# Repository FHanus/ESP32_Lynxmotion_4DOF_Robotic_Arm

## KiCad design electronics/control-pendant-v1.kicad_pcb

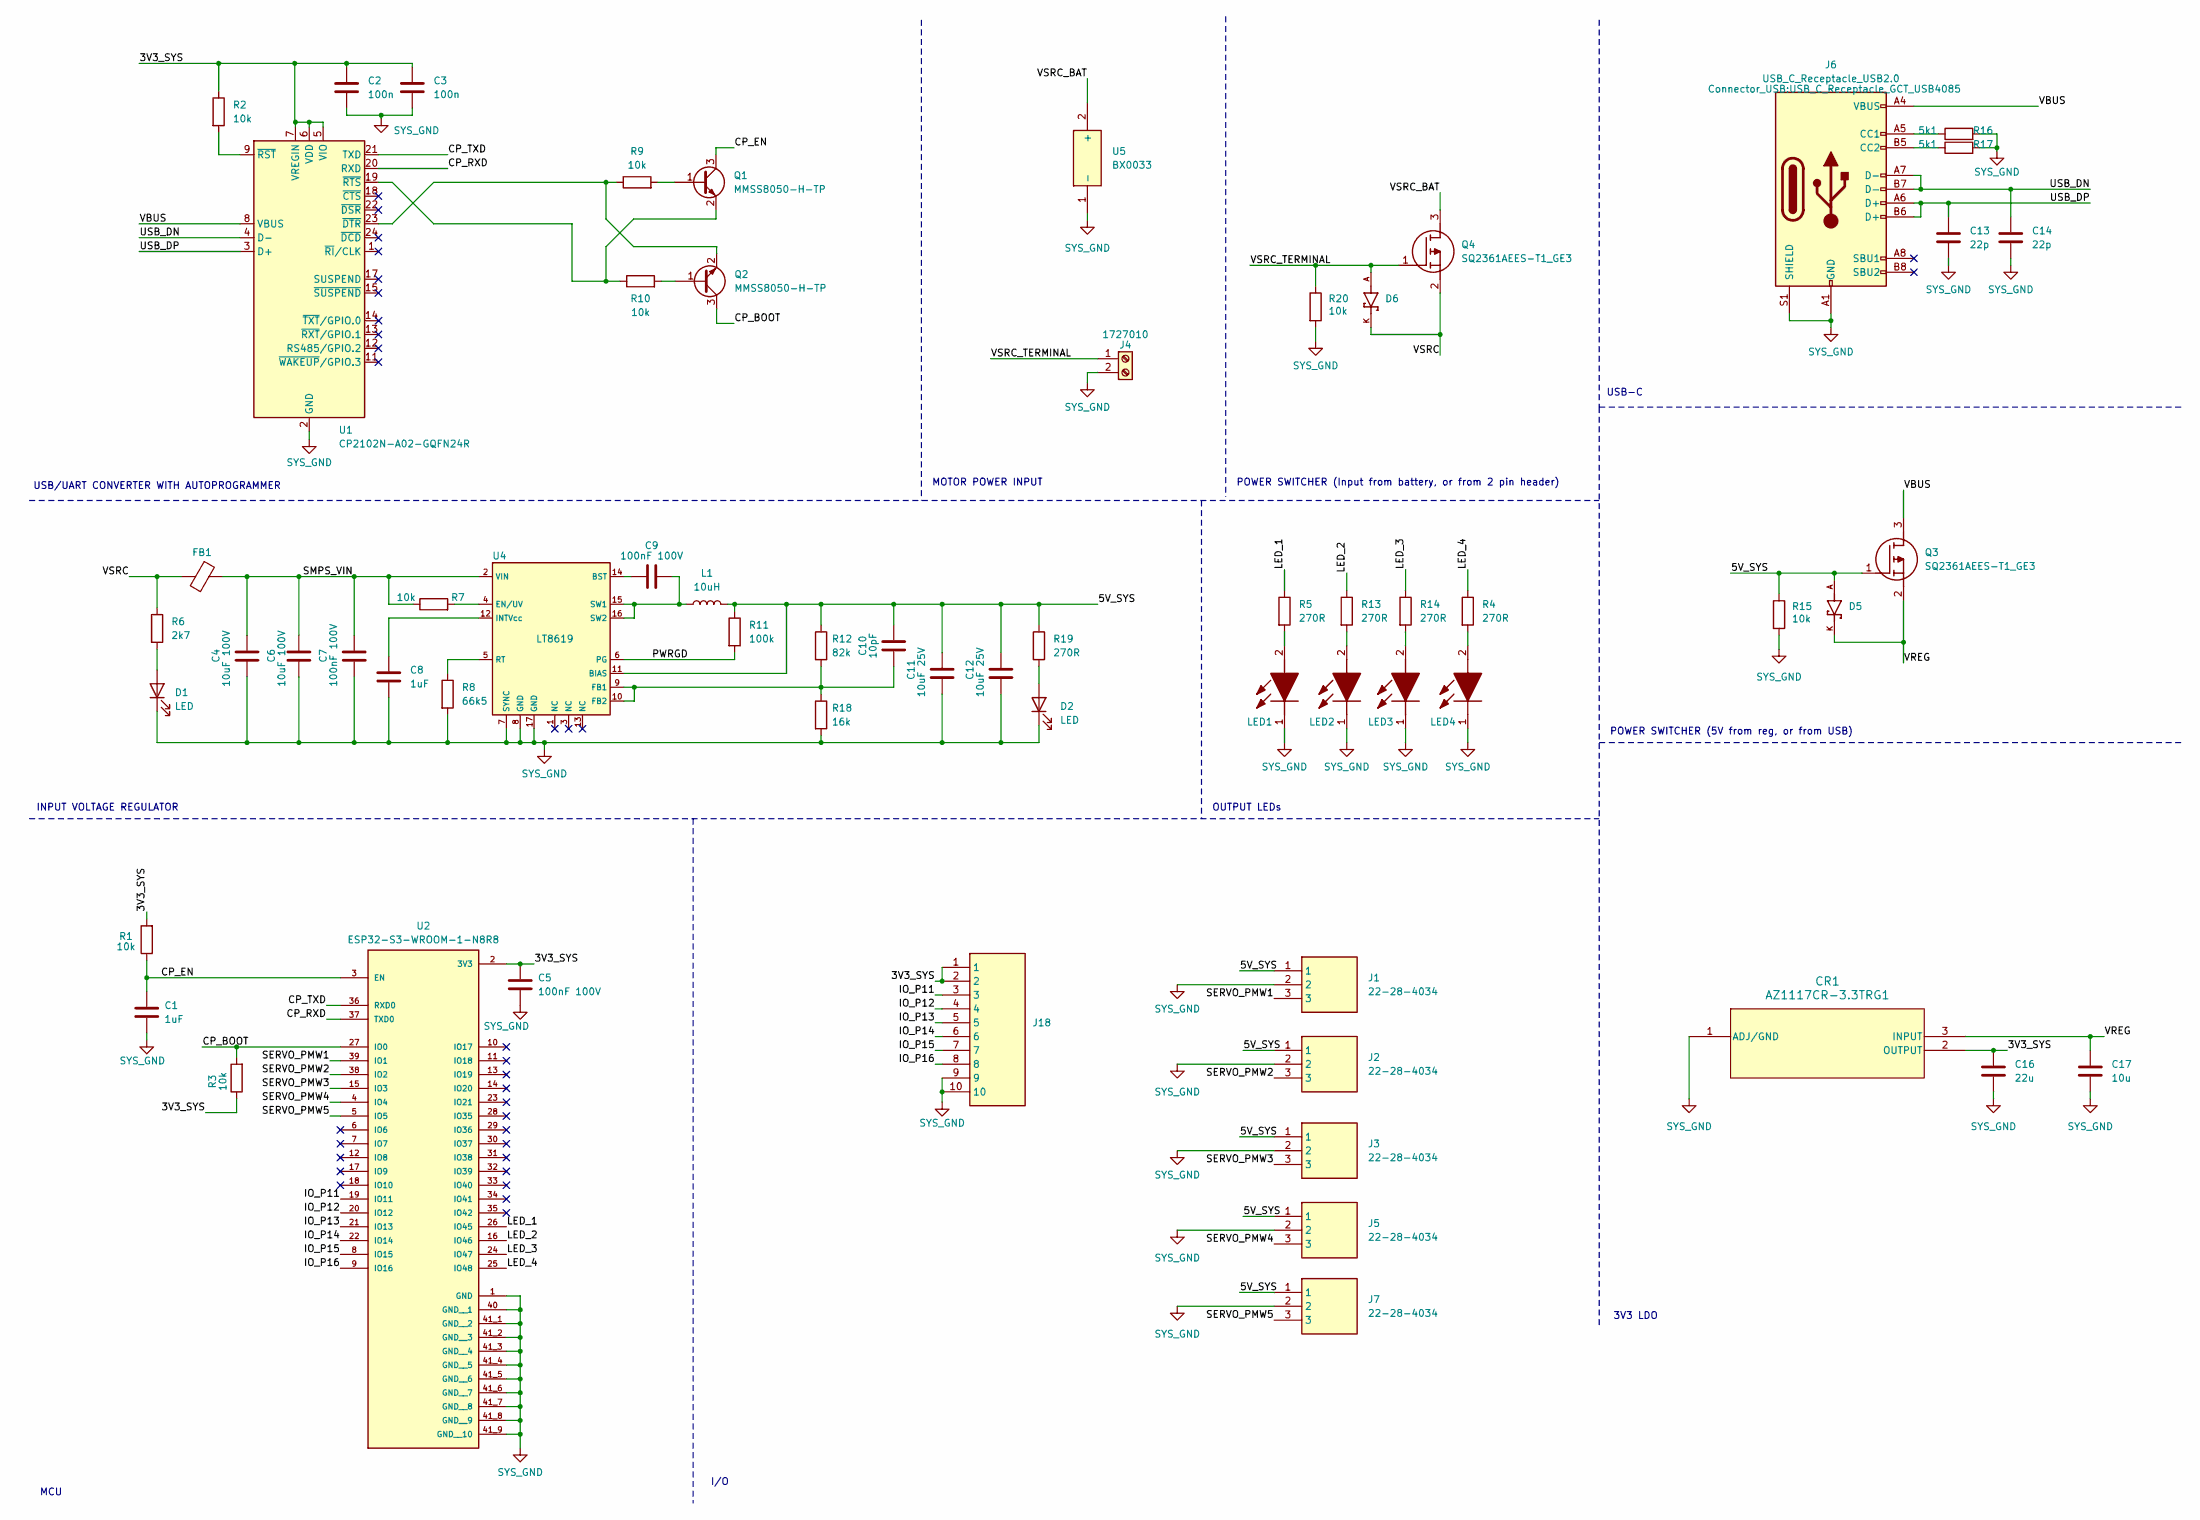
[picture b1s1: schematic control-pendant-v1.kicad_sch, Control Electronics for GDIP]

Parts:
C1, C8: 1uF; C_0603_1608Metric
C2, C3: 100n; C_0402_1005Metric
C4, C6: 10uF 100V; C_1210_3225Metric
C5, C7, C9: 100nF 100V; C_0603_1608Metric
C10: 10pF; C_0603_1608Metric
C11, C12: 10uF 25V; C_0603_1608Metric
C13, C14: 22p; C_0402_1005Metric
C16: 22u; C_0402_1005Metric
C17: 10u; C_0402_1005Metric
CR1: AZ1117CR-3.3TRG1; SOT89_AZ1117_DIO
D1, D2: LED; LED_0603_1608Metric
D5, D6: PMEG3020EH_115; PMEG3020EH_115_DIO_PMEG3020EH_115
FB1: MAF1608GAD121LTAH0; L_0603_1608Metric
J1, J2, J3, J5, J7: 22-28-4034; HDRV3W66P0X254_1X3_762X249X1042P; Mouser Part Number 538-22-28-4034
J4: 1727010
J6: USB_C_Receptacle_USB2.0; USB_C_Receptacle_GCT_USB4085
J18: M20-7821042; SHDR10W70P0X254_1X10_2580X250X865P; Mouser Part Number 855-M20-7821042
L1: 10uH; NRS4018T100MDGJ
LED1, LED2, LED3, LED4: TLHG5420-ASZ; TLHG5420ASZ; Mouser Part Number 78-TLHG5420-ASZ
Q1, Q2: MMSS8050-H-TP; TNPN_SOT-23_MCC
Q3, Q4: SQ2361AEES-T1_GE3; SOT95P237X112-3N; Mouser Part Number 78-SQ2361AEES-T1_GE3
R1, R3, R7: 10k; R_0603_1608Metric
R2, R9, R10, R15, R20: 10k; R_0402_1005Metric
R4, R5, R13, R14: 270R; R_0402_1005Metric
R6: 2k7; R_1206_3216Metric
R8: 66k5; R_0603_1608Metric
R11: 100k; R_0603_1608Metric
R12: 82k; R_0603_1608Metric
R16, R17: 5k1; R_0402_1005Metric
R18: 16k; R_0603_1608Metric
R19: 270R; R_0603_1608Metric
U1: CP2102N-A02-GQFN24R; QFN-24-1EP_4x4mm_P0.5mm_EP2.6x2.6mm
U2: ESP32-S3-WROOM-1-N8R8; ESP32-S3-WROOM-1-N8R8_XCVR_ESP32S3WROOM1N8R8
U4: LT8619; SOP50P490X110-17N
U5: BX0033; Mouser Part Number 122-BX0033

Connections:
/3V3_SYS: C2.1, C3.1, C5.1, C16.1, CR1.2 (OUTPUT), J18.1, J18.2, R1.2, R2.1, R3.1, U1.5 (VIO), U1.6 (VDD), U1.7 (VREGIN), U2.2 (3V3)
/5V_SYS: C10.2, C11.1, C12.1, D5.A, J1.1, J2.1, J3.1, J5.1, J7.1, L1.2, Q3.1 (G), R11.1, R12.1, R15.1, R19.1, U4.11 (BIAS)
/CP_BOOT: Q2.3 (C), R3.2, U2.27 (IO0)
/CP_EN: C1.1, Q1.3 (C), R1.1, U2.3 (EN)
/CP_RXD: U1.20 (RXD), U2.37 (TXD0)
/CP_TXD: U1.21 (TXD), U2.36 (RXD0)
/IO_P11: J18.3, U2.19 (IO11)
/IO_P12: J18.4, U2.20 (IO12)
/IO_P13: J18.5, U2.21 (IO13)
/IO_P14: J18.6, U2.22 (IO14)
/IO_P15: J18.7, U2.8 (IO15)
/IO_P16: J18.8, U2.9 (IO16)
/LED_1: R5.1, U2.26 (IO45)
/LED_2: R13.1, U2.16 (IO46)
/LED_3: R14.1, U2.24 (IO47)
/LED_4: R4.1, U2.25 (IO48)
/PWRGD: R11.2, U4.6 (PG)
/SERVO_PMW1: J1.3, U2.39 (IO1)
/SERVO_PMW2: J2.3, U2.38 (IO2)
/SERVO_PMW3: J3.3, U2.15 (IO3)
/SERVO_PMW4: J5.3, U2.4 (IO4)
/SERVO_PMW5: J7.3, U2.5 (IO5)
/SMPS_VIN: C4.1, C6.1, C7.1, FB1.1, R7.1, U4.2 (VIN)
/USB_DN: C14.1, J6.A7 (D-), J6.B7 (D-), U1.4 (D-)
/USB_DP: C13.1, J6.A6 (D+), J6.B6 (D+), U1.3 (D+)
/VBUS: J6.A4 (VBUS), J6.A9 (VBUS), J6.B4 (VBUS), J6.B9 (VBUS), Q3.3 (D), U1.8 (VBUS)
/VREG: C17.1, CR1.3 (INPUT), D5.K, Q3.2 (S)
/VSRC: D6.K, FB1.2, Q4.2 (S), R6.1
/VSRC_BAT: Q4.3 (D), U5.2 (+)
/VSRC_TERMINAL: D6.A, J4.1, Q4.1 (G), R20.1
unnamed: D1.2 (A), R6.2
unnamed: D2.2 (A), R19.2
unnamed: J6.A5 (CC1), R16.1
unnamed: J6.B5 (CC2), R17.1
unnamed: LED1.2 (A), R5.2
unnamed: LED2.2 (A), R13.2
unnamed: LED3.2 (A), R14.2
unnamed: LED4.2 (A), R4.2
unnamed: Q1.1 (B), R9.2
unnamed: Q1.2 (E), R10.1, U1.19 (~RTS)
unnamed: Q2.1 (B), R10.2
unnamed: Q2.2 (E), R9.1, U1.23 (~DTR)
unnamed: R2.2, U1.9 (~RST)
unnamed: C9.1, U4.14 (BST)
unnamed: R7.2, U4.4 (EN/UV)
unnamed: C10.1, R12.2, R18.1, U4.9 (FB1), U4.10 (FB2)
unnamed: C8.1, U4.12 (INTVcc)
unnamed: R8.1, U4.5 (RT)
unnamed: C9.2, L1.1, U4.15 (SW1), U4.16 (SW2)
SYS_GND: C1.2, C2.2, C3.2, C4.2, C5.2, C6.2, C7.2, C8.2, C11.2, C12.2, C13.2, C14.2, C16.2, C17.2, CR1.1 (ADJ/GND), D1.1 (K), D2.1 (K), J1.2, J2.2, J3.2, J4.2, J5.2, J6.A1 (GND), J6.A12 (GND), J6.B1 (GND), J6.B12 (GND), J6.S1 (SHIELD), J7.2, J18.9, J18.10, LED1.1 (K), LED2.1 (K), LED3.1 (K), LED4.1 (K), R8.2, R15.2, R16.2, R17.2, R18.2, R20.2, U1.2 (GND), U1.25 (GND), U2.1 (GND), U2.40 (GND__1), U2.41_1 (GND__2), U2.41_2 (GND__3), U2.41_3 (GND__4), U2.41_4 (GND__5), U2.41_5 (GND__6), U2.41_6 (GND__7), U2.41_7 (GND__8), U2.41_8 (GND__9), U2.41_9 (GND__10), U2.41_10, U2.41_11, U2.41_12, U2.41_13, U2.41_14, U2.41_15, U2.41_16, U2.41_17, U2.41_18, U2.41_19, U2.41_20, U2.41_21, U4.7 (SYNC), U4.8 (GND), U4.17 (GND), U5.1 (-)

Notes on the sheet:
OUTPUT LEDs
I/O
3V3 LDO
USB/UART CONVERTER WITH AUTOPROGRAMMER
USB-C
POWER SWITCHER (5V from reg, or from USB)
MOTOR POWER INPUT
INPUT VOLTAGE REGULATOR
MCU
POWER SWITCHER (Input from battery, or from 2 pin header)

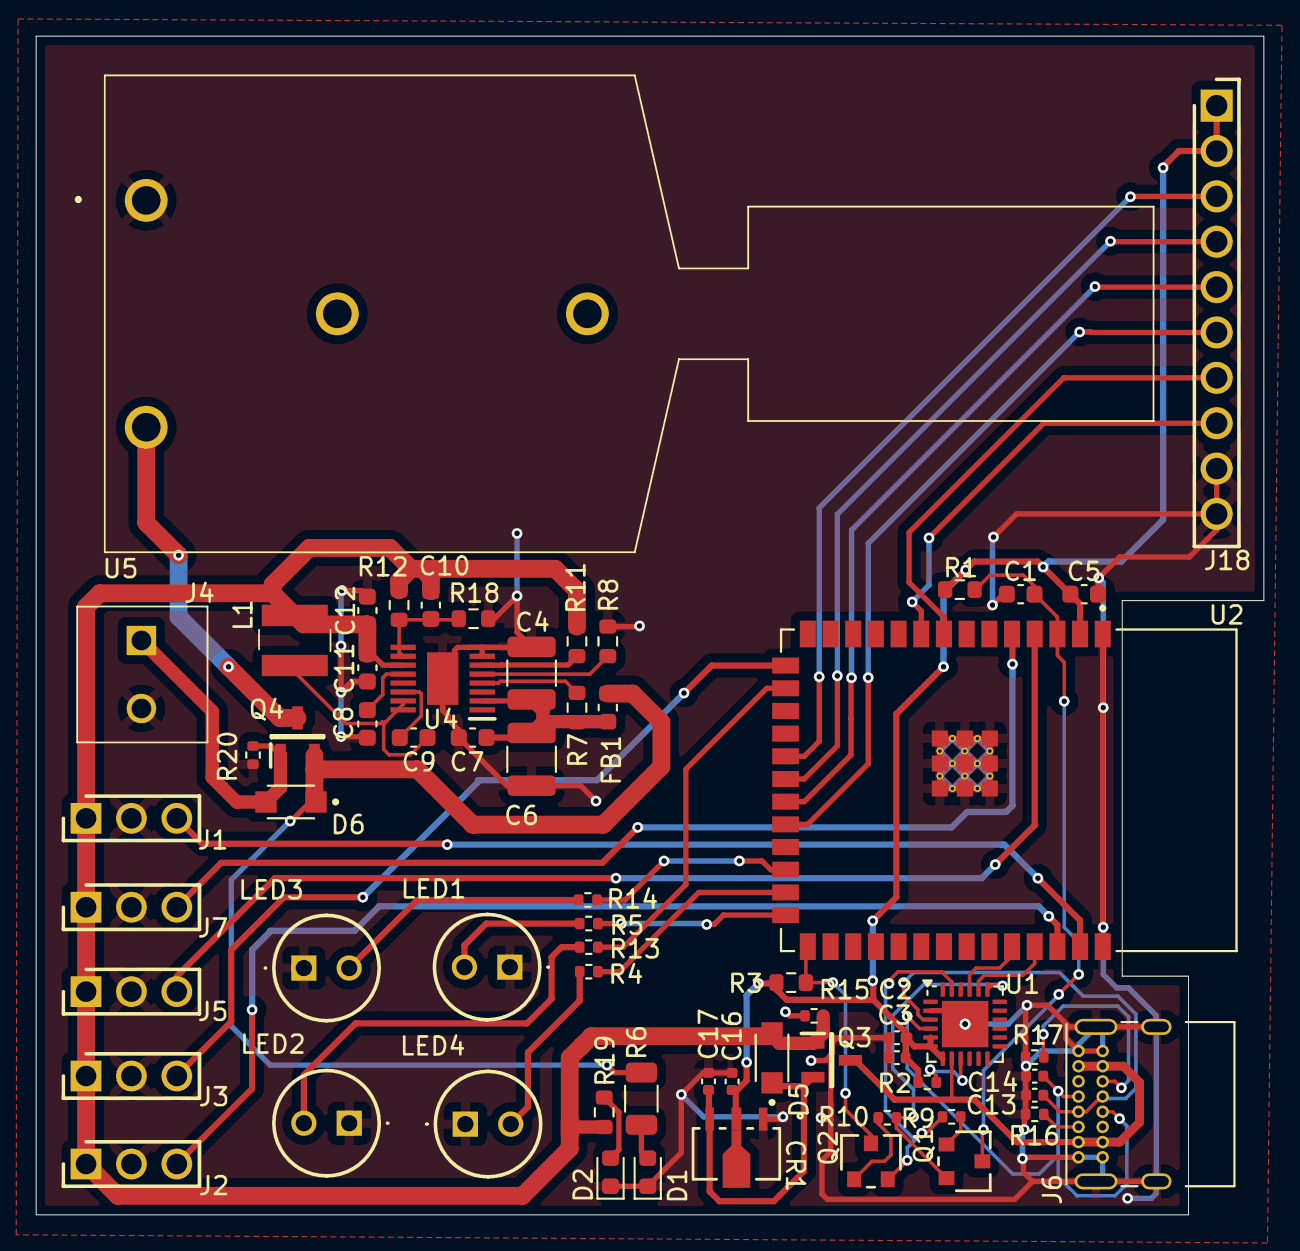
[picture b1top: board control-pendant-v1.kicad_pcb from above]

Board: 2 copper layers, 68.7 x 66.0 mm, 63 parts (0 on the bottom side), 50 nets.

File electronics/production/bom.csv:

Designator,Footprint,Value,Quantity,Link
"C1, C8",603,1uF,2,https://www.mouser.co.uk/ProductDetail/KYOCERA-AVX/06036C105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
C10,603,10pF,1,https://www.mouser.co.uk/ProductDetail/KYOCERA-AVX/0603YA100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
"C11, C12",603,10uF 25V,2,https://www.mouser.co.uk/ProductDetail/Murata-Electronics/GR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
"C13, C14",402,22p,2,https://www.mouser.co.uk/ProductDetail/KYOCERA-AVX/04025A220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
C16,402,22u,1,https://www.mouser.co.uk/ProductDetail/TAIYO-YUDEN/MEASP105C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
C17,402,10u,1,https://www.mouser.co.uk/ProductDetail/Murata-Electronics/GR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
"C2, C3",402,100n,2,https://www.mouser.co.uk/ProductDetail/KYOCERA-AVX/04025C104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
"C4, C6",1210,10uF 100V,2,https://www.mouser.co.uk/ProductDetail/Walsin/1210B106K160CT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
"C5, C7, C9",603,100nF 100V,3,https://www.mouser.co.uk/ProductDetail/TAIYO-YUDEN/MAJCH168B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
CR1,SOT89_AZ1117_DIO,AZ1117CR-3.3TRG1,1,https://www.mouser.co.uk/ProductDetail/Diodes-Incorporated/A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
"D1, D2",603,LED,2,https://www.mouser.co.uk/ProductDetail/VCC/LSM0603412V?qs=%2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
"D5, D6",PMEG3020EH_115_DIO_PMEG3020EH_115,PMEG3020EH_115,2,https://www.mouser.co.uk/ProductDetail/Nexperia/PMEG3020EH11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
FB1,603,MAF1608GAD121LTAH0,1,https://www.mouser.co.uk/ProductDetail/TDK/MAF1608GAD121LTAH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
"J1, J2, J3, J5, J7",HDRV3W66P0X254_1X3_762X249X1042P,22-28-4034,5,
J18,SHDR10W70P0X254_1X10_2580X250X865P,M20-7821042,1,
J4,1727010,1727010,1,
J6,USB_C_Receptacle_GCT_USB4085,USB_C_Receptacle_USB2.0,1,
L1,NRS4018T100MDGJ,10uH,1,https://www.mouser.co.uk/ProductDetail/TAIYO-YUDEN/NRS4018T1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
"LED1, LED2, LED3, LED4",TLHG5420ASZ,TLHG5420-ASZ,4,
"Q1, Q2",TNPN_SOT-23_MCC,MMSS8050-H-TP,2,https://www.mouser.co.uk/ProductDetail/Micro-Commercial-Comp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
"Q3, Q4",SOT95P237X112-3N,SQ2361AEES-T1_GE3,2,https://www.mouser.co.uk/ProductDetail/Vishay-Siliconix/SQ23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
"R1, R3, R7",603,10k,3,https://www.mouser.co.uk/ProductDetail/Vishay-Dale/CRCW06031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
"R10, R15, R2, R20, R9",402,10k,5,https://www.mouser.co.uk/ProductDetail/Vishay-Dale/CRCW04021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
R11,603,100k,1,https://www.mouser.co.uk/ProductDetail/Vishay-Dale/CRCW06031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
R12,603,82k,1,https://www.mouser.co.uk/ProductDetail/Vishay-Dale/CRCW06038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
"R13, R14, R4, R5",402,270R,4,https://www.mouser.co.uk/ProductDetail/Vishay-Dale/CRCW04022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
"R16, R17",402,5k1,2,https://www.mouser.co.uk/ProductDetail/Vishay-Dale/CRCW04025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
R18,603,16k,1,https://www.mouser.co.uk/ProductDetail/Vishay-Dale/CRCW06031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
R19,603,270R,1,https://www.mouser.co.uk/ProductDetail/Vishay-Dale/CRCW06032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
R6,1206,2k7,1,https://www.mouser.co.uk/ProductDetail/Vishay-Dale/CRCW12062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
R8,603,66k5,1,https://www.mouser.co.uk/ProductDetail/Vishay-Dale/CRCW06036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
U1,QFN-24-1EP_4x4mm_P0.5mm_EP2.6x2.6mm,CP2102N-A02-GQFN24R ,1,https://www.mouser.co.uk/ProductDetail/Silicon-Labs/CP2102N-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
U2,ESP32-S3-WROOM-1-N8R8_XCVR_ESP32S3WROOM1N8R8,ESP32-S3-WROOM-1-N8R8,1,https://www.mouser.co.uk/ProductDetail/Espressif-Systems/ESP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
U4,SOP50P490X110-17N,LT8619,1,https://www.digikey.co.uk/en/products/detail/analog-devices-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
U5,BX0033,BX0033,1,https://www.mouser.co.uk/ProductDetail/Bulgin/BX0033?qs=mZhj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

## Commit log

2024-10-12 12/10/2024 - Initial testing code
2024-10-12 12/10/2024 - HTML Page setup and tested
2024-10-12 12/10/2024 - Add buttons for states to website
2024-10-12 12/10/2024 - Add control buttons to the website
2024-10-12 12/10/2024 - Add logic for the buttons on the site, javascript
2024-10-12 12/10/2024 - Add logic for the buttons on the site, javascript, tested
2024-10-12 12/10/2024 - Nitpicks, improve style, linter
2024-10-14 14/10/2024 - Matlab simulation added for the inverse kinematics
2024-11-06 06/11/2024 - State transitions sorted, the IK solutions vary a lot, causing big jumps.
2024-11-06 06/11/2024 - Revert to joint state control for simplicity, potenitally to be changed later.
2024-11-06 06/11/2024 - Fully working code, join positions only
2024-12-08 08/12/2024 electronics
2024-12-08 08/12/2024 functional testing/validation code
2024-12-08 08/12/2024 Testing and validation version
2024-12-09 08/12/2024 Second testing and validation version
2024-12-09 09/12/2024 DONE
2025-01-03 03/01/2025 Cleanup, standardisation
2025-01-03 03/01/2025 Nitpicks, LED
2025-01-05 05/01/2025 Final Commit
